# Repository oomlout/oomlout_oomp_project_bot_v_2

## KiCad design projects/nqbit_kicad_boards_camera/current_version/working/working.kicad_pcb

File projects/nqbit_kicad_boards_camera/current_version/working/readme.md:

# kicad_boards
 
## summary 
* id: nqbit_kicad_boards_camera
* user: nqbit
* name: kicad_boards
* board: camera
* repo: https://github.com/nqbit/kicad-boards
* src_file_repo_kicad_pcb: arduino_template/camera.kicad_pcb
* src_file_repo_kicad_pcb_link: https://github.com/nqbit/kicad-boards/tree/master/arduino_template/camera.kicad_pcb

* src_file_repo_sch: arduino_template/camera.sch
* src_file_repo_sch_link: https://github.com/nqbit/kicad-boards/tree/master/arduino_template/camera.sch
* full details link: https://github.com/oomlout/oomlout_oomp_project_bot_v_2/tree/main/projects/nqbit_kicad_boards_camera/current_version/working

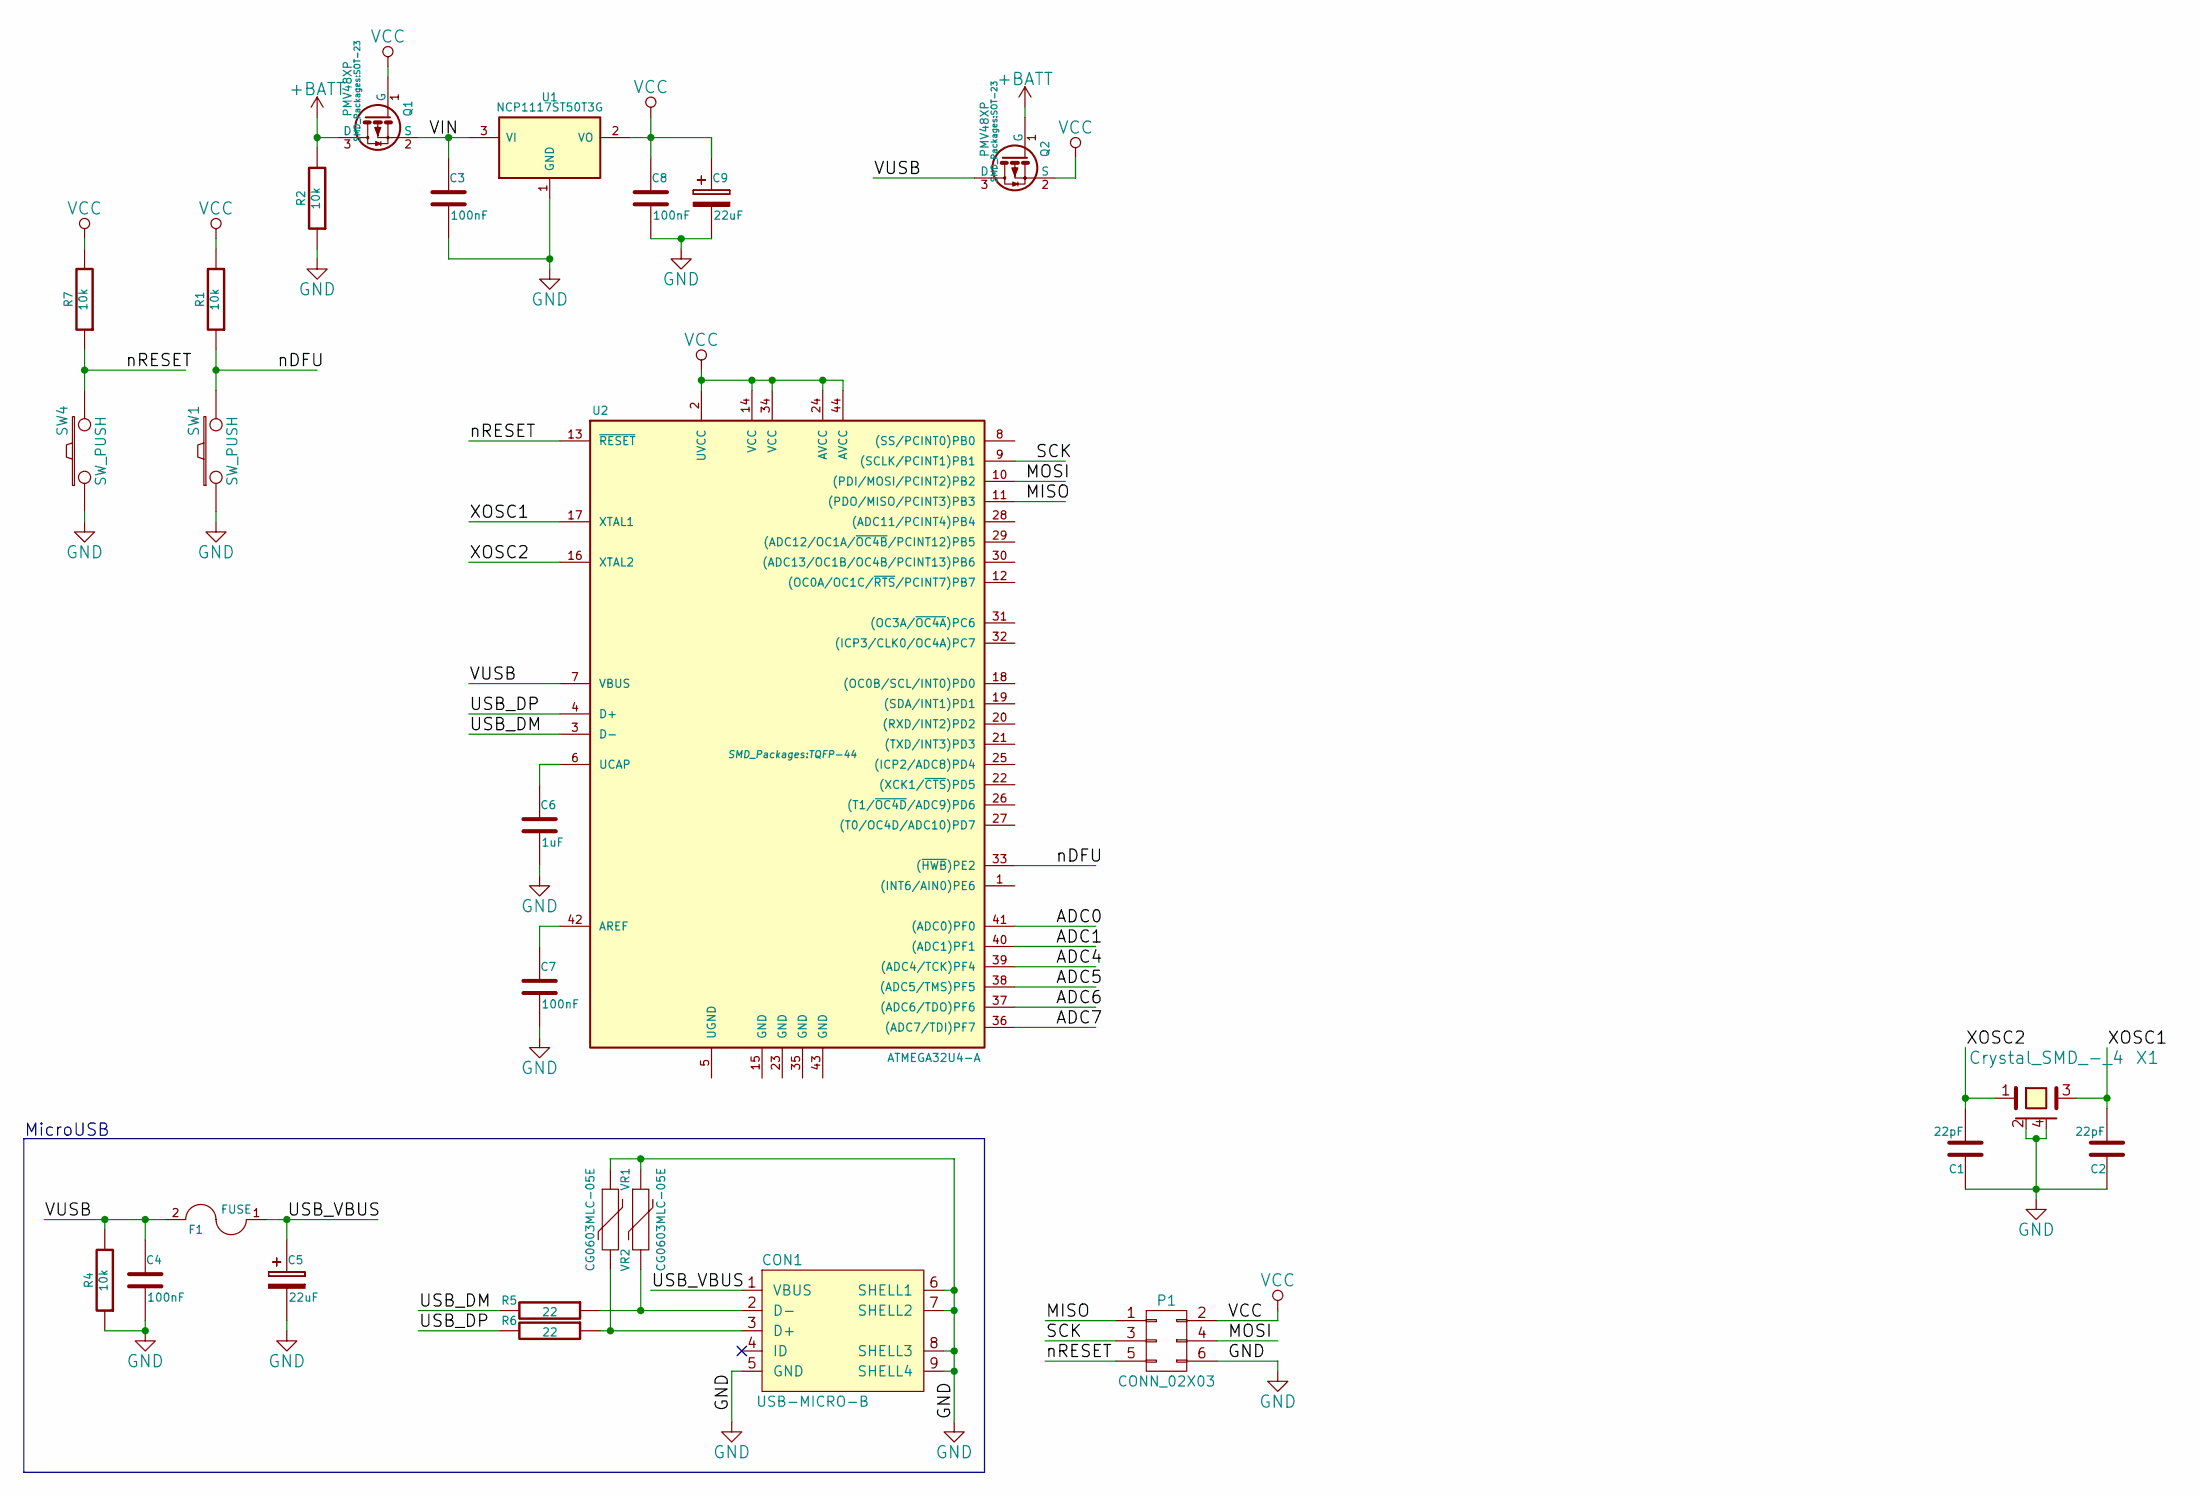
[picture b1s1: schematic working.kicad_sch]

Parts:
C1, C2: 22pF; C_0805
C3, C4, C7, C8: 100nF; C_0805
C5, C9: 22uF; C_1210
C6: 1uF; C_0805
CON1: USB-MICRO-B; USB_Micro-B
F1: FUSE; Fuse_SMD1206_Reflow
P1: CONN_02X03; Pin_Header_Straight_2x03
Q1, Q2: PMV48XP; SOT-23
R1, R2, R4, R7: 10k; R_0805
R5, R6: 22; R_0805
SW1, SW4: SW_PUSH; SW4
U1: NCP1117ST50T3G; SOT-223
U2: ATMEGA32U4-A; TQFP-44
VR1, VR2: CG0603MLC-05E; R_0805
X1: Crystal_SMD_-_4; crystal_FA238-TSX3225

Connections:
+BATT: Q1.3 (D), Q2.1 (G), R2.2
/ADC0: U2.41 ((ADC0)PF0)
/ADC1: U2.40 ((ADC1)PF1)
/ADC4: U2.39 ((ADC4/TCK)PF4)
/ADC5: U2.38 ((ADC5/TMS)PF5)
/ADC6: U2.37 ((ADC6/TDO)PF6)
/ADC7: U2.36 ((ADC7/TDI)PF7)
/MISO: P1.1, U2.11 ((PDO/MISO/PCINT3)PB3)
/MOSI: P1.4, U2.10 ((PDI/MOSI/PCINT2)PB2)
/SCK: P1.3, U2.9 ((SCLK/PCINT1)PB1)
/USB_DM: R5.2, U2.3 (D-)
/USB_DP: R6.2, U2.4 (D+)
/USB_VBUS: C5.1, CON1.1 (VBUS), F1.1
/VIN: C3.1, Q1.2 (S), U1.3 (VI)
/VUSB: C4.1, F1.2, Q2.3 (D), R4.2, U2.7 (VBUS)
/XOSC1: C2.2, U2.17 (XTAL1), X1.3
/XOSC2: C1.2, U2.16 (XTAL2), X1.1
/nDFU: R1.1, SW1.2, U2.33 ((~HWB)PE2)
/nRESET: P1.5, R7.1, SW4.2, U2.13 (~RESET)
GND: C1.1, C2.1, C3.2, C4.2, C5.2, C6.2, C7.2, C8.2, C9.2, CON1.5 (GND), CON1.6 (SHELL1), CON1.7 (SHELL2), CON1.8 (SHELL3), CON1.9 (SHELL4), P1.6, R2.1, R4.1, SW1.1, SW4.1, U1.1 (GND), VR1.1, VR2.1, X1.2, X1.4
unnamed: C6.1, U2.6 (UCAP)
unnamed: C7.1, U2.42 (AREF)
unnamed: CON1.2 (D-), R5.1, VR2.2
unnamed: CON1.3 (D+), R6.1, VR1.2
VCC: C8.1, C9.1, P1.2, Q1.1 (G), Q2.2 (S), R1.2, R7.2, U1.2 (VO), U2.2 (UVCC), U2.14 (VCC), U2.24 (AVCC), U2.34 (VCC), U2.44 (AVCC)

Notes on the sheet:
MicroUSB

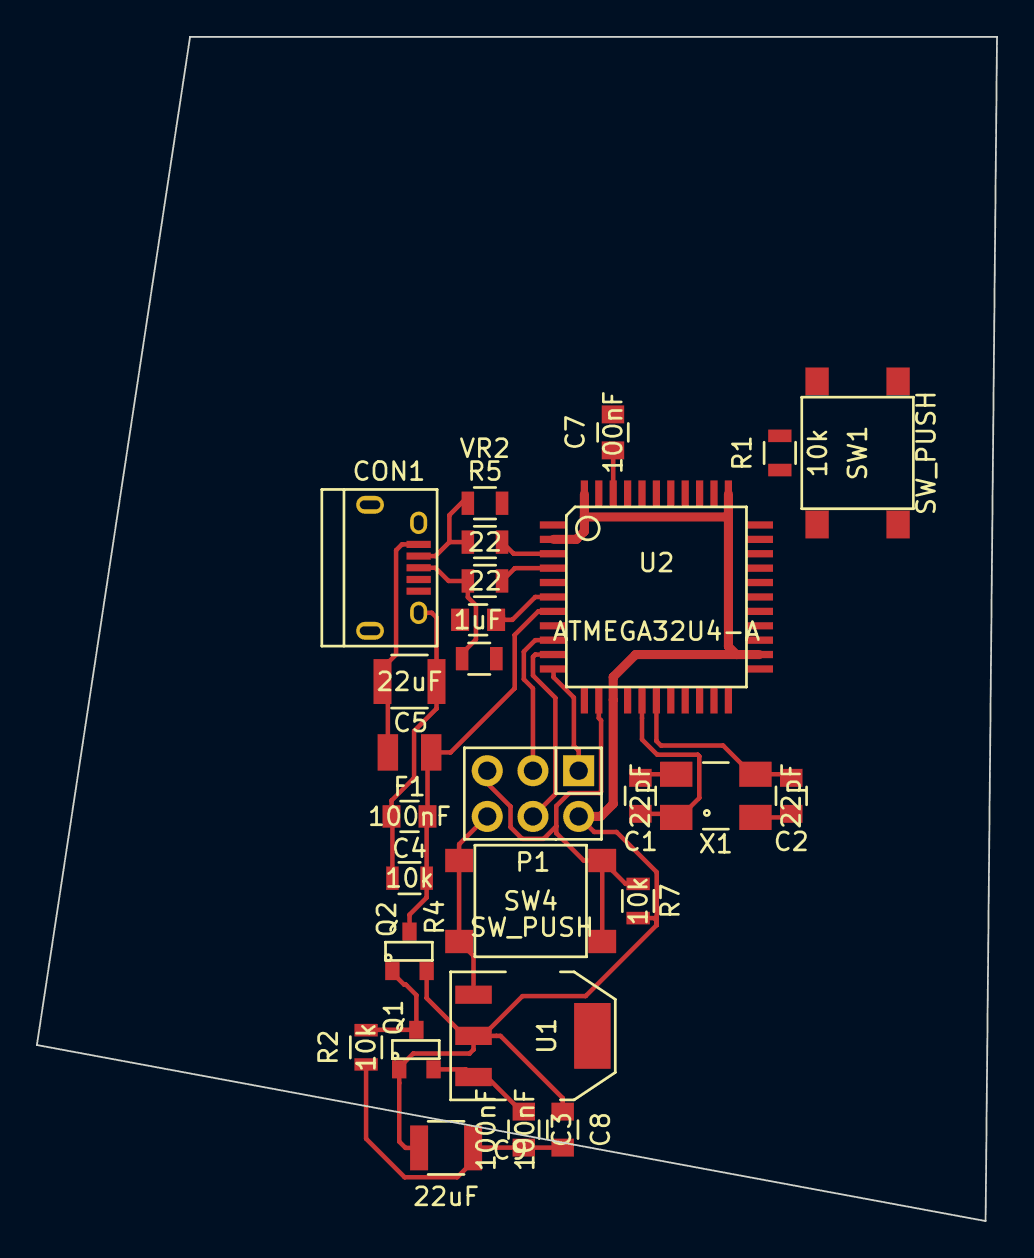
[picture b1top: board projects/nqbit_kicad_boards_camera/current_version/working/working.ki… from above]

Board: 2 copper layers, 53.3 x 65.8 mm, 27 parts (0 on the bottom side), 19 nets.

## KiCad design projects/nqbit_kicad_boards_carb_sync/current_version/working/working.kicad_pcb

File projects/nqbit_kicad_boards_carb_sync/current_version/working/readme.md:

# kicad_boards
 
## summary 
* id: nqbit_kicad_boards_carb_sync
* user: nqbit
* name: kicad_boards
* board: carb_sync
* repo: https://github.com/nqbit/kicad-boards
* src_file_repo_kicad_pcb: carb_sync/V2/carb_sync.kicad_pcb
* src_file_repo_kicad_pcb_link: https://github.com/nqbit/kicad-boards/tree/master/carb_sync/V2/carb_sync.kicad_pcb

* src_file_repo_sch: carb_sync/V2/carb_sync.sch
* src_file_repo_sch_link: https://github.com/nqbit/kicad-boards/tree/master/carb_sync/V2/carb_sync.sch
* full details link: https://github.com/oomlout/oomlout_oomp_project_bot_v_2/tree/main/projects/nqbit_kicad_boards_carb_sync/current_version/working

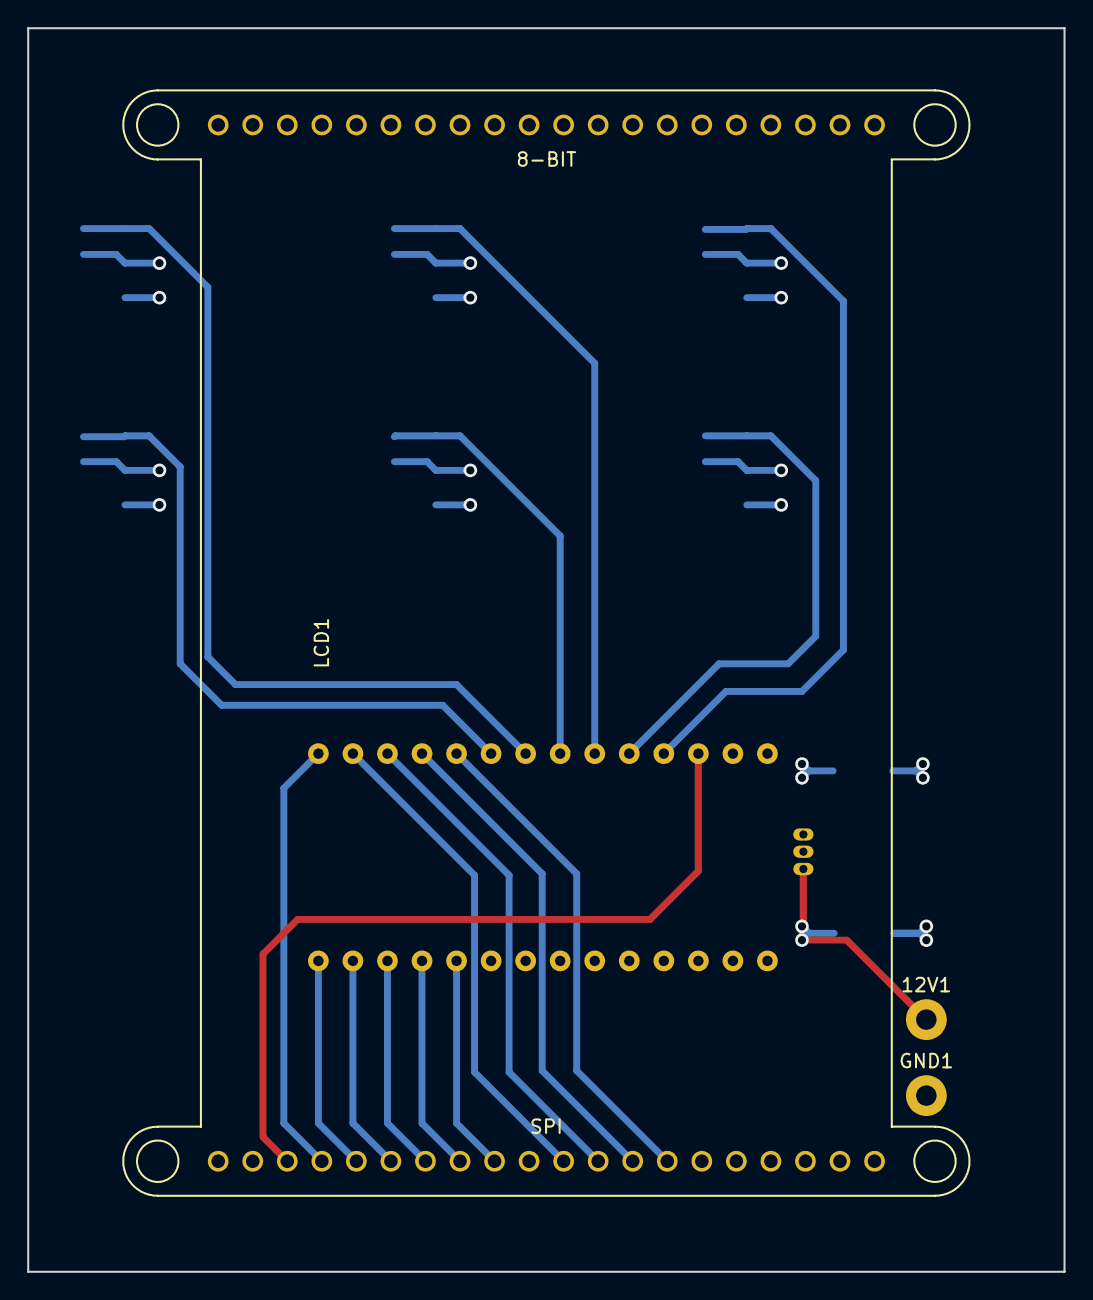
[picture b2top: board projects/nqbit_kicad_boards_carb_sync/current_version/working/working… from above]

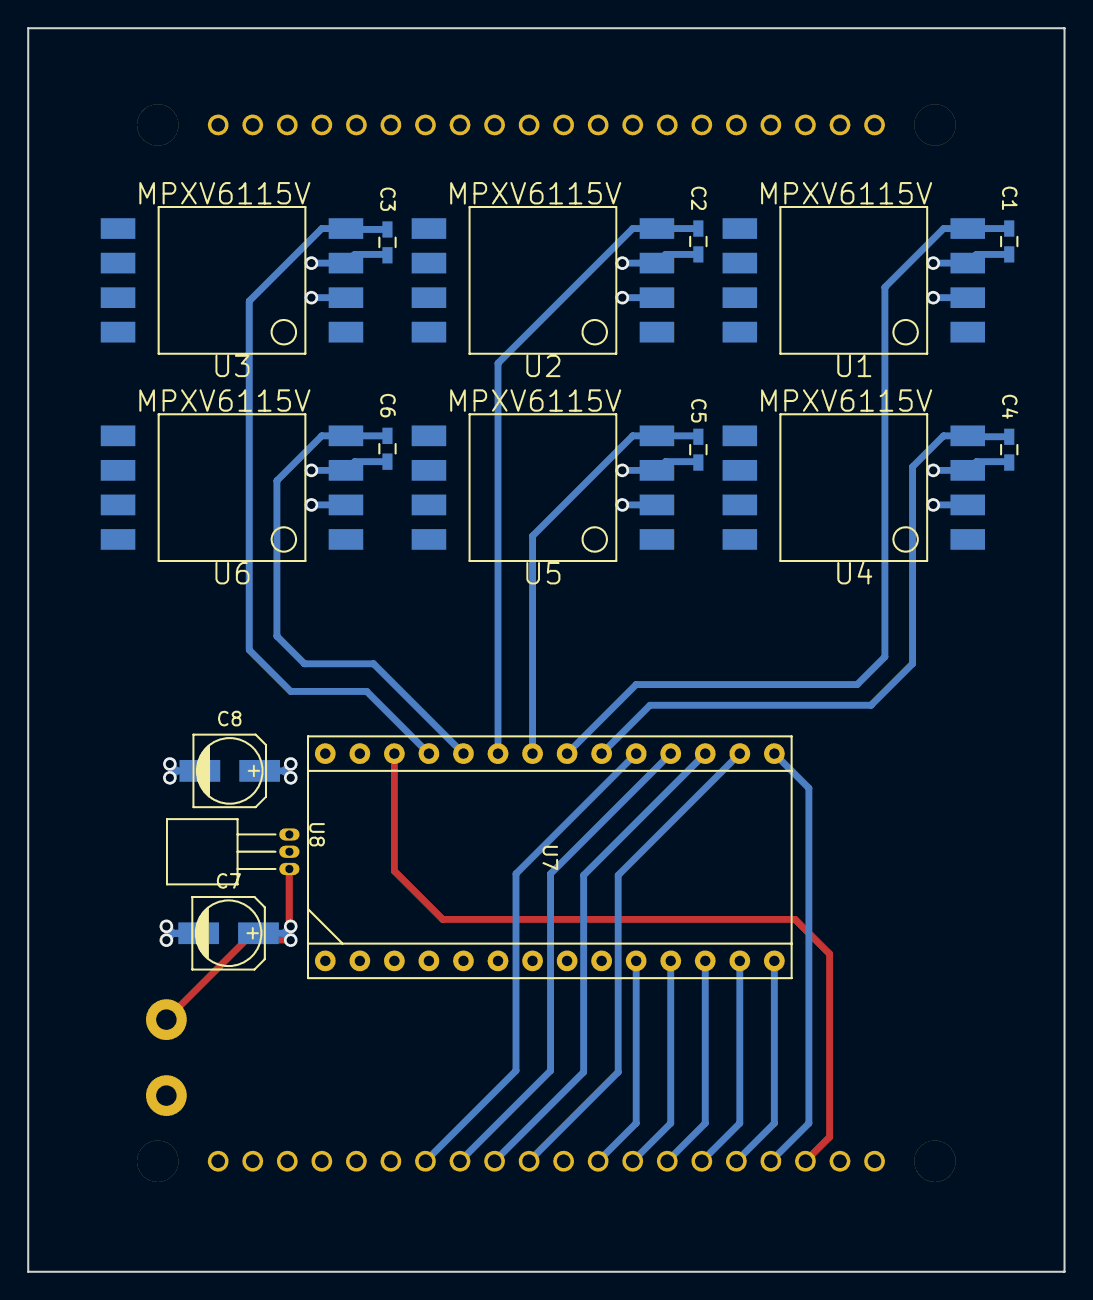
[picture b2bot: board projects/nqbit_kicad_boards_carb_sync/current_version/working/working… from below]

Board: 4 copper layers, 76.2 x 91.4 mm, 19 parts (16 on the bottom side), 20 nets.

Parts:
12V1: 12V; Measurement_Point_Round-TH_Big
C1, C2, C3, C4, C5, C6: 100nF; C_0603_HandSoldering
C7, C8: C; c_elec_5x5.7
GND1: GND; Measurement_Point_Round-TH_Big
LCD1: ILI9341_Adafruit; ADAFRUIT_LCD
U1, U2, U3, U4, U5, U6: MPXV6115V
U7: TEENSY_3.2
U8: AP1117; TO-92_Horizontal1_Inline_Narrow_Oval

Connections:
+3V3: LCD1.3, U7.26
+5V: C8.1, LCD1.2, LCD1.39, U1.2, U2.2, U3.2, U4.2, U5.2, U6.2, U7.28, U8.2
+12V: 12V1.1, C7.1, U8.3
GND: C1.2, C2.2, C3.2, C4.2, C5.2, C6.2, C7.2, C8.2, GND1.1, LCD1.1, LCD1.40, U1.3, U2.3, U3.3, U4.3, U5.3, U6.3, U7.1, U7.27, U8.1
LCD_CLK: LCD1.4, U7.15
LCD_CS: LCD1.7, U7.12
LCD_D/C: LCD1.8, U7.11
LCD_MISO: LCD1.5, U7.14
LCD_MOSI: LCD1.6, U7.13
LCD_RST: LCD1.9, U7.10
TOUCH_X+: LCD1.12, U7.17
TOUCH_X-: LCD1.14, U7.19
TOUCH_Y+: LCD1.11, U7.16
TOUCH_Y-: LCD1.13, U7.18
VAC1: C1.1, U1.4, U7.21
VAC2: C2.1, U2.4, U7.23
VAC3: C3.1, U3.4, U7.25
VAC4: C4.1, U4.4, U7.20
VAC5: C5.1, U5.4, U7.22
VAC6: C6.1, U6.4, U7.24

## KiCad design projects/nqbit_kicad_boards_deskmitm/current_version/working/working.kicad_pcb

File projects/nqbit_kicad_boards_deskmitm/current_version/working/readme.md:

# kicad_boards
 
## summary 
* id: nqbit_kicad_boards_deskmitm
* user: nqbit
* name: kicad_boards
* board: deskmitm
* repo: https://github.com/nqbit/kicad-boards
* src_file_repo_kicad_pcb: deskmitm/deskmitm.kicad_pcb
* src_file_repo_kicad_pcb_link: https://github.com/nqbit/kicad-boards/tree/master/deskmitm/deskmitm.kicad_pcb

* src_file_repo_sch: deskmitm/deskmitm.sch
* src_file_repo_sch_link: https://github.com/nqbit/kicad-boards/tree/master/deskmitm/deskmitm.sch
* full details link: https://github.com/oomlout/oomlout_oomp_project_bot_v_2/tree/main/projects/nqbit_kicad_boards_deskmitm/current_version/working

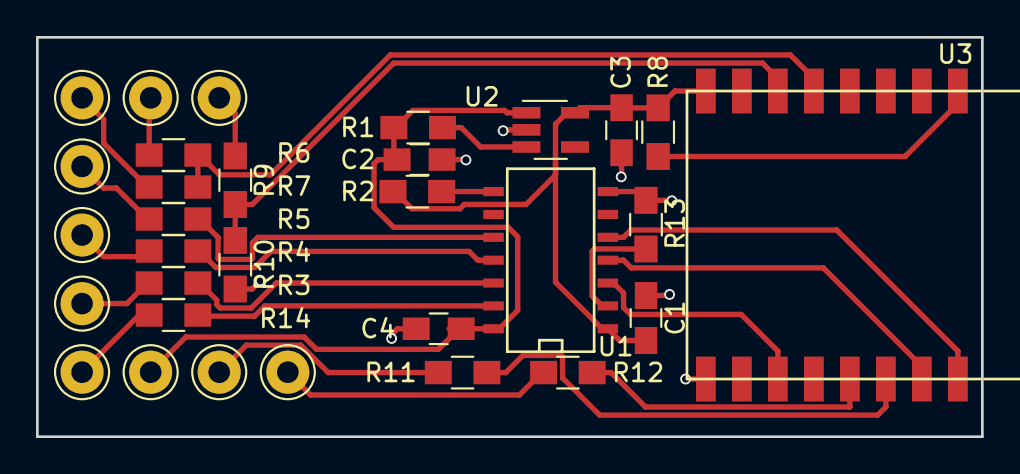
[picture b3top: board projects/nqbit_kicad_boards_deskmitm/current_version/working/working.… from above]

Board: 2 copper layers, 52.5 x 22.2 mm, 31 parts (0 on the bottom side), 26 nets.

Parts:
C1, C4: 100nF; C_0805_HandSoldering
C2, C3: 10uF; C_0805_HandSoldering
J1, J2, J3, J4, J5, J6, J7, J8, J9, J10: Conn_01x01; Pin_d1.0mm_L10.0mm_LooseFit
R1, R2, R8, R11, R12, R13: 10k; R_0805_HandSoldering
R3, R4, R5, R6, R9, R14: 1k; R_0805_HandSoldering
R7, R10: 2k; R_0805_HandSoldering
U1: TXB0104; SOIC-14_N
U2: AP2112; SOT-23-5_HandSoldering
U3: ESP8266_12S; ESP8266_07

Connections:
+3V3: C1.1, C3.1, R2.2, R8.1, U1.1, U2.5, U3.8
+5V: C2.1, C4.1, J9.1, R1.2, U1.14, U2.1
/BTN_DOWN_IN: J1.1, R6.1
/BTN_DOWN_IN_LV: R6.2, R7.1, U3.5
/BTN_DOWN_OUT: J4.1, R12.1
/BTN_UP_IN: J2.1, R9.1
/BTN_UP_IN_LV: R9.2, R10.1, U3.6
/BTN_UP_OUT: J3.1, R11.1
/RX_FROM_POWER: J8.1, R5.1
/RX_FROM_POWER_LV: U1.5, U3.16
/RX_TO_DISPLAY: J5.1, R14.1
/RX_TO_DISPLAY_LV: R13.1, U1.2
/TX_FROM_POWER: J7.1, R4.1
/TX_FROM_POWER_LV: U1.4, U3.15
/TX_TO_DISPLAY: J6.1, R3.1
/TX_TO_DISPLAY_LV: U1.3, U3.11
GND: C1.2, C2.2, C3.2, C4.2, J10.1, R7.2, R10.2, R13.2, U1.7, U2.2, U3.9
unnamed: R1.1, U2.3
unnamed: R2.1, U1.8
unnamed: R3.2, U1.12
unnamed: R4.2, U1.11
unnamed: R5.2, U1.10
unnamed: R8.2, U3.1
unnamed: R11.2, U3.14
unnamed: R12.2, U3.13
unnamed: R14.2, U1.13

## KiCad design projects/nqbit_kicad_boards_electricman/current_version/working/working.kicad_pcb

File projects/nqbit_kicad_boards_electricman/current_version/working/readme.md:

# kicad_boards
 
## summary 
* id: nqbit_kicad_boards_electricman
* user: nqbit
* name: kicad_boards
* board: electricman
* repo: https://github.com/nqbit/kicad-boards
* src_file_repo_kicad_pcb: electricman/electricman.kicad_pcb
* src_file_repo_kicad_pcb_link: https://github.com/nqbit/kicad-boards/tree/master/electricman/electricman.kicad_pcb

* src_file_repo_sch: electricman/electricman.sch
* src_file_repo_sch_link: https://github.com/nqbit/kicad-boards/tree/master/electricman/electricman.sch
* full details link: https://github.com/oomlout/oomlout_oomp_project_bot_v_2/tree/main/projects/nqbit_kicad_boards_electricman/current_version/working

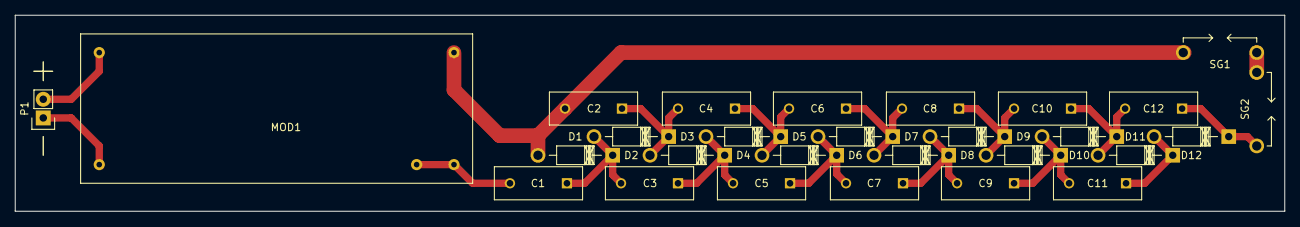
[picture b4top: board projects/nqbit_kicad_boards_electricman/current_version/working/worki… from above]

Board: 2 copper layers, 172.7 x 26.7 mm, 28 parts (0 on the bottom side), 17 nets.

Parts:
C1, C2, C3, C4, C5, C6, C7, C8, C9, C10, C11, C12: C; C_Disc_D12_P7.75
D1, D2, D3, D4, D5, D6, D7, D8, D9, D10, D11, D12: D; Diode_DO-41_SOD81_Horizontal_RM10
MOD1: ROYER; Royer
P1: CONN_01X02; Pin_Header_Straight_1x02
SG1, SG2: SparkGap

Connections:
GND: MOD1.2, P1.1
HV+: C12.1, D12.1, SG2.2
HV-: SG1.2, SG2.1
HV_GND: C2.2, D1.2, MOD1.5, SG1.1
HV_SUPPLY: C1.2, MOD1.3, MOD1.4
unnamed: C1.1, C3.2, D1.1, D2.2
unnamed: C2.1, C4.2, D2.1, D3.2
unnamed: C3.1, C5.2, D3.1, D4.2
unnamed: C4.1, C6.2, D4.1, D5.2
unnamed: C5.1, C7.2, D5.1, D6.2
unnamed: C6.1, C8.2, D6.1, D7.2
unnamed: C7.1, C9.2, D7.1, D8.2
unnamed: C10.1, C12.2, D10.1, D11.2
unnamed: C8.1, C10.2, D8.1, D9.2
unnamed: C11.1, D11.1, D12.2
unnamed: C9.1, C11.2, D9.1, D10.2
VCC: MOD1.1, P1.2

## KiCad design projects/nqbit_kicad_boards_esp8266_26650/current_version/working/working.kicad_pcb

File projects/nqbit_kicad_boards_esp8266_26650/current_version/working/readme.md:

# kicad_boards
 
## summary 
* id: nqbit_kicad_boards_esp8266_26650
* user: nqbit
* name: kicad_boards
* board: esp8266_26650
* repo: https://github.com/nqbit/kicad-boards
* src_file_repo_kicad_pcb: esp8266_26650/esp8266_26650.kicad_pcb
* src_file_repo_kicad_pcb_link: https://github.com/nqbit/kicad-boards/tree/master/esp8266_26650/esp8266_26650.kicad_pcb

* src_file_repo_sch: esp8266_26650/esp8266_26650.sch
* src_file_repo_sch_link: https://github.com/nqbit/kicad-boards/tree/master/esp8266_26650/esp8266_26650.sch
* full details link: https://github.com/oomlout/oomlout_oomp_project_bot_v_2/tree/main/projects/nqbit_kicad_boards_esp8266_26650/current_version/working

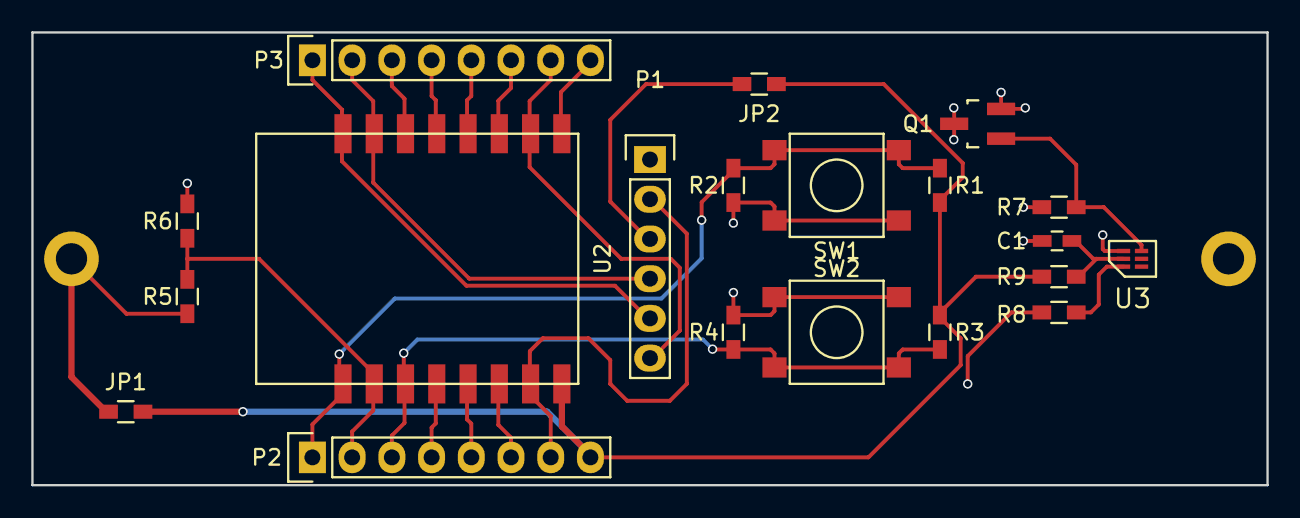
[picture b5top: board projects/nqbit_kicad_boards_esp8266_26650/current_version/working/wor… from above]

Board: 2 copper layers, 79.0 x 29.0 mm, 21 parts (1 on the bottom side), 22 nets.

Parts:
C1: 0.1uF; C_0603_HandSoldering
JP1, JP2: JUMPER; R_0603_HandSoldering
P1: CONN_01X06; Pin_Header_Straight_1x06
P2, P3: CONN_01X08; Pin_Header_Straight_1x08
Q1: MMBF170; SOT-23_Handsoldering
R1, R2, R3, R4: 10k; R_0603_HandSoldering
R5: 260k; R_0603_HandSoldering
R6: 100k; R_0603_HandSoldering
R7: 5.1M; R_0603_HandSoldering
R8: 2.2k; R_0603_HandSoldering
R9: 330; R_0603_HandSoldering
SW1, SW2: SW_PUSH; B3S-1000P
U1: BATT_26650x1
U2: ESP8266_07
U3: BQ29705; WFDFN-6

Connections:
+BATT: JP1.1, R5.1, U1.1
/CH_PD: P2.3, R3.2, R4.1, SW2.2, U2.3
/DOUT: Q1.1, R7.1, U3.3
/FTDI_CTS: P1.2, P2.7, U2.7
/FTDI_RTS: P1.6, P3.7, U2.10
/FTDI_RX: P1.5, P3.1, U2.16
/FTDI_TX: P1.4, P3.2, U2.15
/FTDI_VCC: JP2.2, P1.3
/GPIO0: P3.5, U2.12
/GPIO1: P3.6, U2.11
/GPIO4: P3.4, U2.13
/GPIO5: P3.3, U2.14
/GPIO12: P2.6, U2.6
/GPIO14: P2.5, U2.5
/RESET: P2.1, R1.2, R2.1, SW1.2, U2.1
/VBAT_MON: P2.2, R5.2, R6.1, U2.2
/WAKE: P2.4, U2.4
GND: P1.1, P3.8, Q1.3, R2.2, R4.2, R6.2, R8.1, SW1.1, SW2.1, U2.9
unnamed: C1.1, R9.2, U3.5
unnamed: R8.2, U3.6
VCC: JP1.2, JP2.1, P2.8, R1.1, R3.1, R9.1, U2.8
VSS: C1.2, Q1.2, R7.2, U1.2, U3.4

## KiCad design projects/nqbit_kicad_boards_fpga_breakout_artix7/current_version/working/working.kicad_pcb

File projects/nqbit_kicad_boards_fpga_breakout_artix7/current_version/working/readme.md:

# kicad_boards
 
## summary 
* id: nqbit_kicad_boards_fpga_breakout_artix7
* user: nqbit
* name: kicad_boards
* board: fpga_breakout_artix7
* repo: https://github.com/nqbit/kicad-boards
* src_file_repo_kicad_pcb: fpga_breakout_artix7/fpga_breakout_artix7.kicad_pcb
* src_file_repo_kicad_pcb_link: https://github.com/nqbit/kicad-boards/tree/master/fpga_breakout_artix7/fpga_breakout_artix7.kicad_pcb

* src_file_repo_sch: esp8266_26650/esp8266_26650.sch
* src_file_repo_sch_link: https://github.com/nqbit/kicad-boards/tree/master/esp8266_26650/esp8266_26650.sch
* full details link: https://github.com/oomlout/oomlout_oomp_project_bot_v_2/tree/main/projects/nqbit_kicad_boards_fpga_breakout_artix7/current_version/working

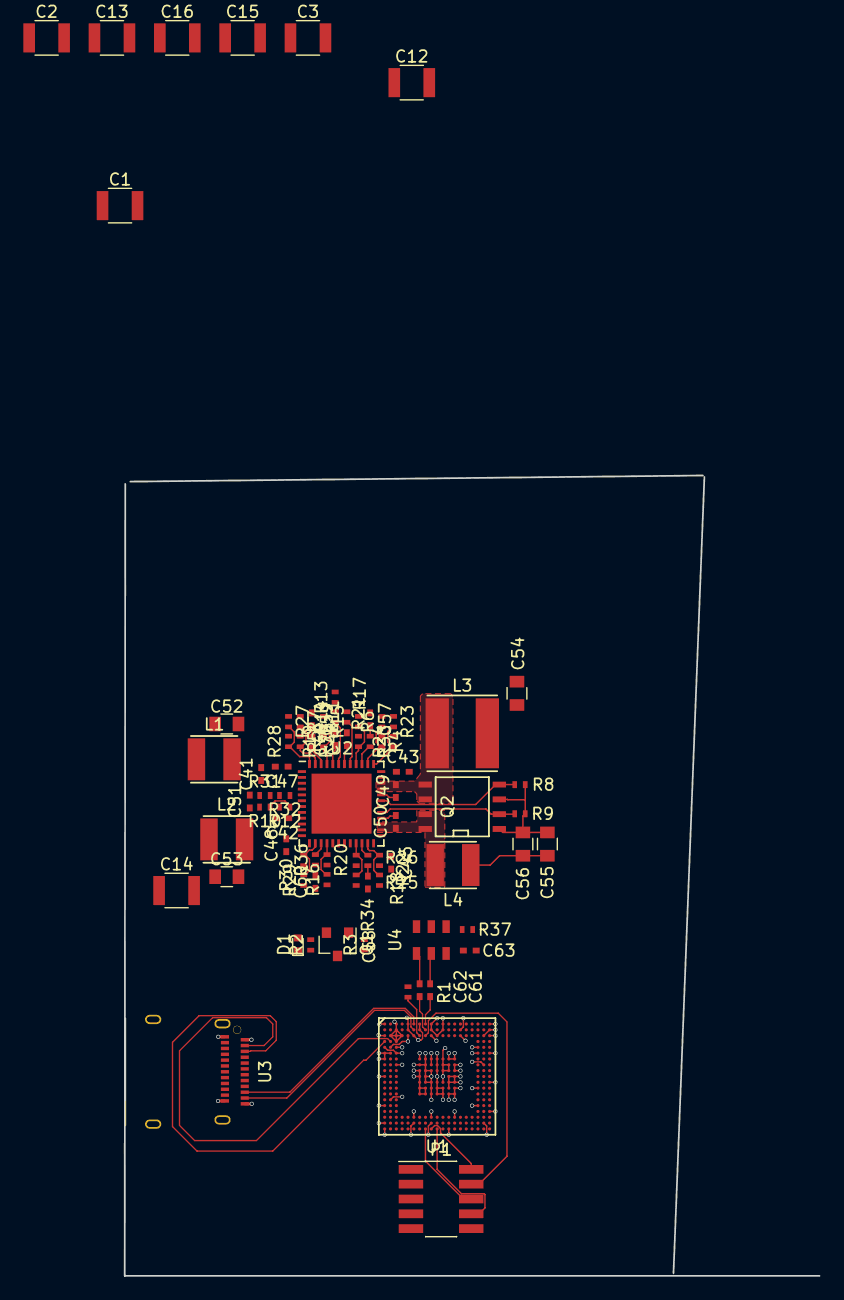
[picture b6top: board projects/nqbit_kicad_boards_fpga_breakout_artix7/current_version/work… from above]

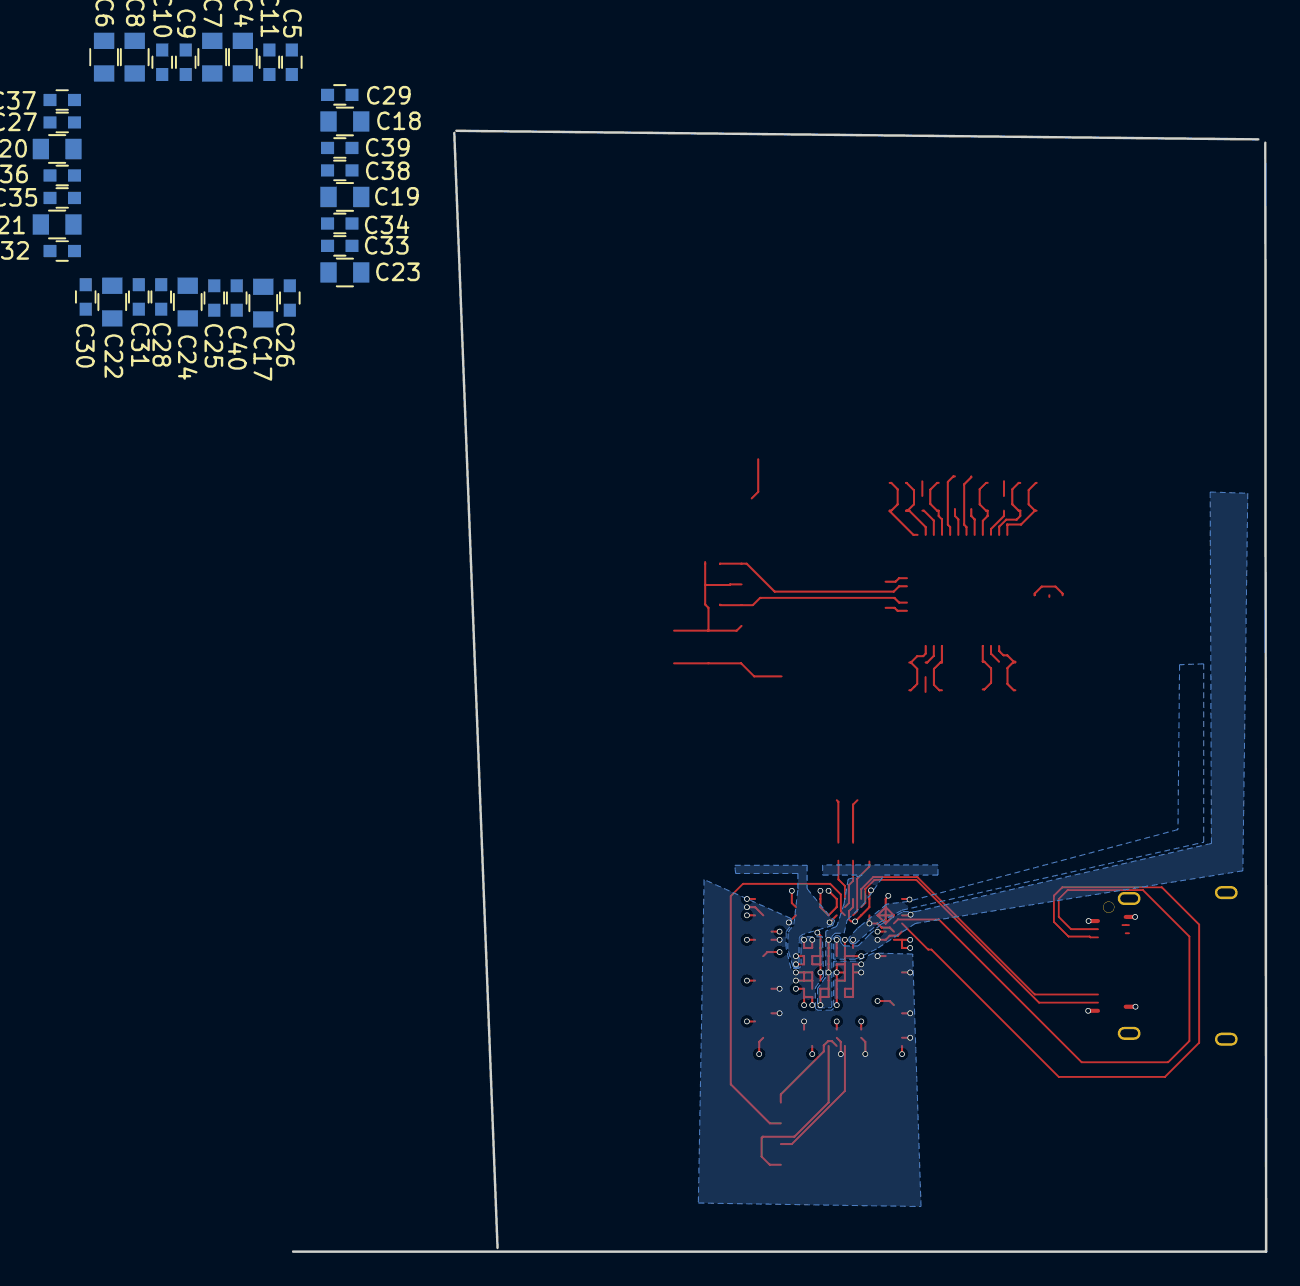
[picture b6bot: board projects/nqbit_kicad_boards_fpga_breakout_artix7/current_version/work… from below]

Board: 4 copper layers, 59.6 x 68.6 mm, 112 parts (32 on the bottom side), 68 nets.

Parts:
C1, C13, C14, C15, C16: 100uF; C_1210
C2, C3, C12: 47uF; C_1210
C4, C6, C7, C8, C17, C18, C19, C20, C21, C22, C23, C24: 4.7uF; C_0805
C5, C9, C10, C11, C25, C26, C27, C28, C29, C30, C31, C32, C33, C34, C35, C36, C37, C38, C39, C40: 0.47uF; C_0603
C41, C42, C43, C44, C45, C46, C51: 1uF; C_0402_NoSilk
C47, C48, C49, C50, C61, C62, C63: 100nF; C_0402_NoSilk
C52, C53: 10uF; C_0805
C54: 100uF; C_0805
C55, C56: 22uF; C_0805
C57, C58, C59, C60: 2.7nF; C_0402_NoSilk
D1: LED; LED_0402
L1, L2: 4.7uH; SRN4018
L3: 2.2uH; SRN6045
L4: 3.3uH; SRN4018
P1: CONN_02X05; Pin_Header_Straight_2x05_Pitch1.27mm_SMD
Q1: MOSFET-N; SOT-23
Q2: FDS9926A; SOIC-8-N
R1: 100; R_0402_NoSilk
R2: 4.7k; R_0402_NoSilk
R3: 100k; R_0402_NoSilk
R4, R13: 0; R_0402_NoSilk
R5: 301k; R_0402_NoSilk
R6: 9.53k - DNP; R_0402_NoSilk
R7: 402k; R_0402_NoSilk
R8, R9: 47k; R_0402_NoSilk
R10: 1.91k; R_0402_NoSilk
R11, R17: 31.6k; R_0402_NoSilk
R12: 4.99k; R_0402_NoSilk
R14: 0 - DNP; R_0402_NoSilk
R15, R18: 10.5k; R_0402_NoSilk
R16, R21: 10.2k; R_0402_NoSilk
R19, R22: 41.2k; R_0402_NoSilk
R20: 20k; R_0402_NoSilk
R23, R24, R25, R26, R27, R28, R29, R30, R31, R32, R33, R34, R35, R36: 56.2k; R_0402_NoSilk
R37: 10k; R_0402_NoSilk
U1: XC7A15TCPG236; CPG236
U2: ADP5052; QFN-48-1EP_7x7mm_Pitch0.5mm
U3: USB-C; USB-C_SMT
U4: DSC1123

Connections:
/GTP0_RX_N: U1.A4, U3.B10
/GTP0_RX_P: U1.B4, U3.B11
/GTP0_TX_N: U1.D1, U3.A3
/GTP0_TX_P: U1.D2, U3.A2
/GTP1_RX_N: U1.A6, U3.A10
/GTP1_RX_P: U1.B6, U3.A11
/GTP1_TX_N: U1.A2, U3.B3
/GTP1_TX_P: U1.B2, U3.B2
/GTP_REF_CLK_N: C61.1, U1.A8
/GTP_REF_CLK_P: C62.1, U1.B8
/JTAG_TCK: P1.4, U1.C8
/JTAG_TDI: P1.8, U1.W10
/JTAG_TDO: P1.6, U1.W8
/JTAG_TMS: P1.2, U1.W9
/VCC3V3: C63.2, P1.1, R37.1, U4.6
/power/AVCC1V0: C52.1, L1.2, R15.1
/power/AVCC1V2: C53.1, L2.2, R16.1
/power/BST1: C49.1, U2.32
/power/BST2: C50.1, U2.28
/power/COMP1: R33.2, U2.39
/power/COMP2: R34.2, U2.22
/power/COMP3: R35.2, U2.46
/power/COMP4: R36.2, U2.15
/power/DL1: Q2.4, R8.2, U2.31
/power/DL2: Q2.2, R9.2, U2.29
/power/EN1: R23.2, R24.1, U2.37
/power/EN2: R25.2, R26.1, U2.23
/power/EN3: R27.2, R28.1, U2.48
/power/EN4: R29.2, R30.1, U2.14
/power/EN5: R31.2, R32.1, U2.5
/power/FB1: R17.2, R21.1, U2.40
/power/FB2: R18.2, R22.1, U2.21
/power/FB3: R15.2, R19.1, U2.45
/power/FB4: R16.2, R20.1, U2.16
/power/FB5: R10.1, R12.1, U2.6
/power/SS12: R4.2, R6.1, U2.38
/power/SS34: R5.2, R7.2, U2.47
/power/SW1: C49.2, L3.1, Q2.5, Q2.6, U2.33, U2.34
/power/SW2: C50.2, L4.1, Q2.7, Q2.8, U2.26, U2.27
/power/SW3: C47.2, L1.1, U2.3
/power/SW4: C48.2, L2.1, U2.10
/power/VCC1V0: C55.1, C56.1, L4.2, R18.1
/power/VCC1V8: C51.1, R12.2, U2.7
/power/VCC3V3: C54.1, D1.2, L3.2, R3.1, R17.1, R23.1, R25.1, R27.1, R29.1, R31.1, U2.8
/power/VCC5V0: C41.1, C42.1, C43.1, C45.1, U2.4, U2.9, U2.24, U2.25, U2.35, U2.36
/power/VREG: C44.1, R6.2, R7.1, R13.2, U2.44
AVCC1P0: U1.C1, U1.E1, U1.F3, U1.G9, U1.H9
AVCC1P2: R1.2, U1.B1, U1.C5, U1.E2, U1.G7
GND: C1.2, C2.2, C3.2, C4.2, C5.2, C6.2, C7.2, C8.2, C9.2, C10.2, C11.2, C12.2, C13.2, C14.2, C15.2, C16.2, C17.2, C18.2, C19.2, C20.2, C21.2, C22.2, C23.2, C24.2, C25.2, C26.2, C27.2, C28.2, C29.2, C30.2, C31.2, C32.2, C33.2, C34.2, C35.2, C36.2, C37.2, C38.2, C39.2, C40.2, C41.2, C42.2, C43.2, C44.2, C45.2, C46.2, C51.2, C52.2, C53.2, C54.2, C55.2, C56.2, C57.1, C58.1, C59.1, C60.1, C63.1, P1.3, P1.5, P1.9, Q1.3, Q2.1, Q2.3, R4.1, R5.1, R8.1, R9.1, R10.2, R11.2, R14.2, R19.2, R20.2, R21.2, R22.2, R24.2, R26.2, R28.2, R30.2, R32.2, U1.A1, U1.A3, U1.A5, U1.A7, U1.A9, U1.A11, U1.A19, U1.B3, U1.B5, U1.B7, U1.B9, U1.B11, U1.B14, U1.C2, U1.C3, U1.C4, U1.C6, U1.C10, U1.C19, U1.D3, U1.E3, U1.E17, U1.F1, U1.F2, U1.F19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
unnamed: C46.1, U2.42
unnamed: C47.1, U2.1
unnamed: C48.1, U2.12
unnamed: C57.2, R33.1
unnamed: C58.2, R34.1
unnamed: C59.2, R35.1
unnamed: C60.2, R36.1
unnamed: C61.2, U4.5
unnamed: C62.2, U4.4
unnamed: D1.1, R2.1
unnamed: Q1.1, R3.2, U2.20
unnamed: Q1.2, R2.2
unnamed: R1.1, U1.C7
unnamed: R11.1, U2.41
unnamed: R13.1, R14.1, U2.43
unnamed: R37.2, U4.1
V1P0: C1.1, C2.1, C4.1, C5.1, C7.1, C9.1, C11.1, U1.G10, U1.H10, U1.J10, U1.L10, U1.M10, U1.M11, U1.N10, U1.N11
V1P8: C3.1, C6.1, C8.1, C10.1, U1.C9, U1.H13, U1.J13
V3P3: C12.1, C13.1, C14.1, C15.1, C16.1, C17.1, C18.1, C19.1, C20.1, C21.1, C22.1, C23.1, C24.1, C25.1, C26.1, C27.1, C28.1, C29.1, C30.1, C31.1, C32.1, C33.1, C34.1, C35.1, C36.1, C37.1, C38.1, C39.1, C40.1, U1.B19, U1.C14, U1.C18, U1.F17, U1.G12, U1.G13, U1.H3, U1.J7, U1.K1, U1.K7, U1.K12, U1.K13, U1.L7, U1.L12, U1.L13, U1.M7, U1.M8, U1.M12, U1.M17, U1.N7, U1.N8, U1.R1, U1.R17, U1.U13, U1.V1, U1.V6, U1.V9

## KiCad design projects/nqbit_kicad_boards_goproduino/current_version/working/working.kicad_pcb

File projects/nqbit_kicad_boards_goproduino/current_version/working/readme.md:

# kicad_boards
 
## summary 
* id: nqbit_kicad_boards_goproduino
* user: nqbit
* name: kicad_boards
* board: goproduino
* repo: https://github.com/nqbit/kicad-boards
* src_file_repo_kicad_pcb: goproduino/goproduino.kicad_pcb
* src_file_repo_kicad_pcb_link: https://github.com/nqbit/kicad-boards/tree/master/goproduino/goproduino.kicad_pcb

* src_file_repo_sch: goproduino/goproduino.sch
* src_file_repo_sch_link: https://github.com/nqbit/kicad-boards/tree/master/goproduino/goproduino.sch
* full details link: https://github.com/oomlout/oomlout_oomp_project_bot_v_2/tree/main/projects/nqbit_kicad_boards_goproduino/current_version/working

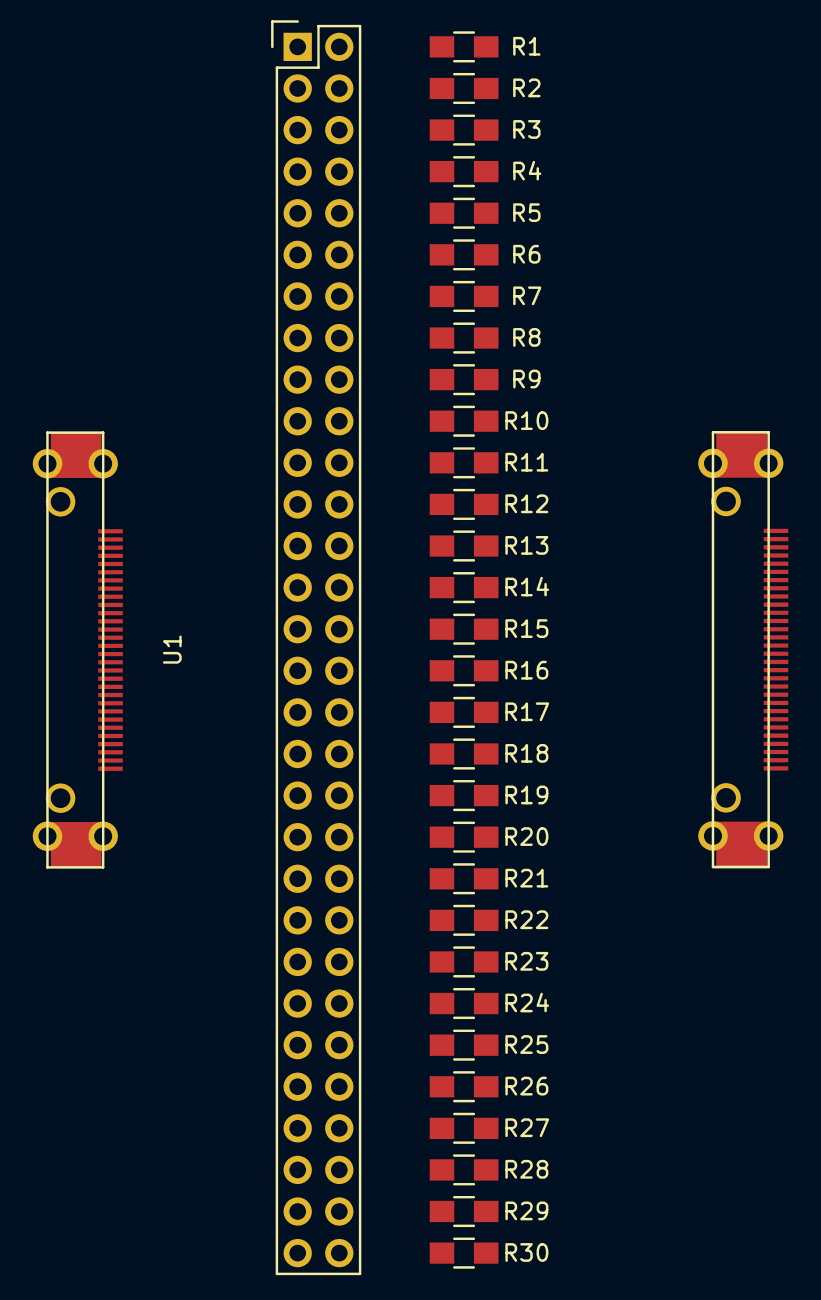
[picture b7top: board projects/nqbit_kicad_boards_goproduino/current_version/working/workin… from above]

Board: 2 copper layers, 33 parts (0 on the bottom side), 84 nets, no tracks yet.

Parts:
P1: CONN_02X30; Pin_Header_Straight_2x30
R1, R2, R3, R4, R5, R6, R7, R8, R9, R10, R11, R12, R13, R14, R15: 0; R_0805_HandSoldering
R16, R17, R18, R19, R20, R21, R22, R23, R24, R25, R26, R27, R28, R29, R30: R; R_0805_HandSoldering
U1, U2: gopro; DD1B030HA1R500

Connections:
/BATTERY_IN: P1.50, P1.52, R25.2, R26.2
/B_PR_CR_VIDEO_OUT: P1.8, R4.2
/CAM_BATTERY_IN: P1.49, P1.51, U1.25, U1.26
/CAM_B_PR_CR_VIDEO_OUT: P1.7, U1.4
/CAM_GND0: P1.1, U1.1
/CAM_GND1: P1.17, U1.9
/CAM_GND2: P1.35, U1.18
/CAM_GND3: P1.53, U1.27
/CAM_GND4: P1.59, U1.30
/CAM_G_Y_VIDEO_OUT: P1.5, U1.3
/CAM_I2C_CLOCK: P1.57, U1.29
/CAM_I2C_DATA: P1.55, U1.28
/CAM_ID1: P1.37, U1.19
/CAM_ID2: P1.39, U1.20
/CAM_ID3: P1.41, U1.21
/CAM_ID4: P1.43, U1.22
/CAM_IR_IN: P1.31, U1.16
/CAM_L_AUDIO_IN: P1.29, U1.15
/CAM_L_AUDIO_OUT: P1.21, U1.11
/CAM_PB_CB_VIDEO_OUT: P1.3, U1.2
/CAM_PLAYBACK: P1.25, U1.13
/CAM_POWER_MODE_BUTTON: P1.23, U1.12
/CAM_POWER_OUT: P1.47, U1.24
/CAM_POWER_OUT_STANDBY: P1.45, U1.23
/CAM_R_AUDIO_IN: P1.27, U1.14
/CAM_R_AUDIO_OUT: P1.19, U1.10
/CAM_TRIGGER: P1.33, U1.17
/CAM_USB_DATA_N: P1.15, U1.8
/CAM_USB_DATA_P: P1.13, U1.7
/CAM_USB_POWER: P1.9, P1.11, U1.5, U1.6
/DEV_BATTERY_IN: R25.1, R26.1, U2.25, U2.26
/DEV_B_PR_CR_VIDEO_OUT: R4.1, U2.4
/DEV_GND0: R1.1, U2.1
/DEV_GND1: R9.1, U2.9
/DEV_GND2: R18.1, U2.18
/DEV_GND3: R27.1, U2.27
/DEV_GND4: R30.1, U2.30
/DEV_G_Y_VIDEO_OUT: R3.1, U2.3
/DEV_I2C_CLOCK: R29.1, U2.29
/DEV_I2C_DATA: R28.1, U2.28
/DEV_ID1: R19.1, U2.19
/DEV_ID2: R20.1, U2.20
/DEV_ID3: R21.1, U2.21
/DEV_ID4: R22.1, U2.22
/DEV_IR_IN: R16.1, U2.16
/DEV_L_AUDIO_IN: R15.1, U2.15
/DEV_L_AUDIO_OUT: R11.1, U2.11
/DEV_PB_CB_VIDEO_OUT: R2.1, U2.2
/DEV_PLAYBACK: R13.1, U2.13
/DEV_POWER_MODE_BUTTON: R12.1, U2.12
/DEV_POWER_OUT: R24.1, U2.24
/DEV_POWER_OUT_STANDBY: R23.1, U2.23
/DEV_R_AUDIO_IN: R14.1, U2.14
/DEV_R_AUDIO_OUT: R10.1, U2.10
/DEV_TRIGGER: R17.1, U2.17
/DEV_USB_DATA_N: R8.1, U2.8
/DEV_USB_DATA_P: R7.1, U2.7
/DEV_USB_POWER: R5.1, R6.1, U2.5, U2.6
/GND0: P1.2, R1.2
/GND1: P1.18, R9.2
/GND2: P1.36, R18.2
/GND3: P1.54, R27.2
/GND4: P1.60, R30.2
/G_Y_VIDEO_OUT: P1.6, R3.2
/I2C_CLOCK: P1.58, R29.2
/I2C_DATA: P1.56, R28.2
/ID1: P1.38, R19.2
/ID2: P1.40, R20.2
/ID3: P1.42, R21.2
/ID4: P1.44, R22.2
/IR_IN: P1.32, R16.2
/L_AUDIO_IN: P1.30, R15.2
/L_AUDIO_OUT: P1.22, R11.2
/PB_CB_VIDEO_OUT: P1.4, R2.2
/PLAYBACK: P1.26, R13.2
/POWER_MODE_BUTTON: P1.24, R12.2
/POWER_OUT: P1.48, R24.2
/POWER_OUT_STANDBY: P1.46, R23.2
/R_AUDIO_IN: P1.28, R14.2
/R_AUDIO_OUT: P1.20, R10.2
/TRIGGER: P1.34, R17.2
/USB_DATA_N: P1.16, R8.2
/USB_DATA_P: P1.14, R7.2
/USB_POWER: P1.10, P1.12, R5.2, R6.2
